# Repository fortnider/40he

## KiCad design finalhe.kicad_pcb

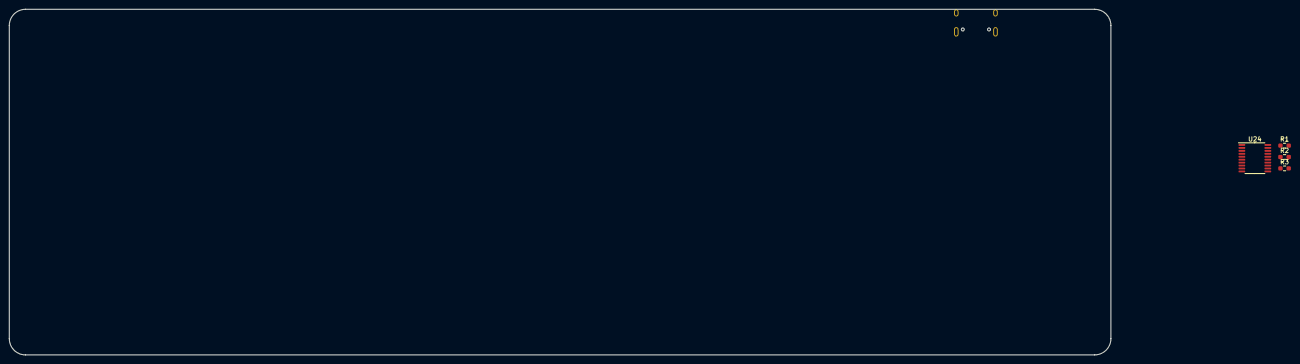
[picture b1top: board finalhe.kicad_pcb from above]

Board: 2 copper layers, 242.9 x 76.2 mm, 5 parts (1 on the bottom side), 6 nets, no tracks yet.

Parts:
P1: USB_C_Plug_USB2.0; USB_C_Receptacle_HRO_TYPE-C-31-M-12
R1, R2: 5.1k; R_0603_1608Metric_Pad0.98x0.95mm_HandSolder
R3: 1k5; R_0603_1608Metric_Pad0.98x0.95mm_HandSolder
U24: STM32F070F6Px; TSSOP-20_4.4x6.5mm_P0.65mm

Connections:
+5V: P1.A4 (VBUS), P1.A9 (VBUS), P1.B4 (VBUS), P1.B9 (VBUS)
D+: P1.A6 (D+), R3.1
GND: P1.A1 (GND), P1.A12 (GND), P1.B1 (GND), P1.B12 (GND), P1.S1 (SHIELD), R1.2, R2.2, U24.15 (VSS)
unnamed: P1.A5 (CC), R2.1
unnamed: P1.B5 (VCONN), R1.1
VDD: R3.2, U24.16 (VDD)

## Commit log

2023-12-15 fdsf
2023-12-17 fdsfkjsdh
2023-12-19 fdsb
